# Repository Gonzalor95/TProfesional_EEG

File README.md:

# TProfesional_EEG

Trabajo Profesional para la carrera de Ingeniería Electrónica de FIUBA

Alumnos:
Rizzo Gonzalo
Davila Galesio Ignacio
Carosella Juan Manuel

Este repositorio contiene los archivos de software (codigo fuente y simulacion) generados para el trabajo final. Se divide en dos carpetas:

- CubeIDE_projects contiene los archivos relacionados a la programación y configuracion del microcontrolador junto con el software escrito para el mismo
- Proteus_projects contiene los archivos de simulacion

# Notas de reuniones

## 21/10/2021

Objetivo final: reproducción de muestras de 1 hora en total.
 * Agregar en la GUI la posibilidad de elegir el tiempo de reproducción
 * Considerar para el tema de la alimentación

Otras cuestiones:
* Analizar alternativas del BluePill. Capaz algo más potente, tiene más documentación, etc.
* Evaluar alternativa de mandar los datos de la PC al micro es utilizar en vez de USB, usar un protocolo inalámbrico. (ver si se puede realizar una adaptación para utilizar el celular para mandar los datos)
* Analizar Nice-to-have la utilización del celular para usar el dispositivo. Para este caso, es conveniente desarrollar la comunicación inalámbrica con el Microcontrolador.
* Analizar Linux driver: https://wiki.analog.com/resources/tools-software/linux-drivers/iio-dac/ad5360
 ** La familia de Nano puede ser que los drivers no sean solamente de Linux (investigar).
* Analizar el pin de LATCH en los DACs para sacar los datos de forma sincrónica. Si no hay Latch, investigar alternativa de como solucionarlo (enviar todos los canales de forma sincrónica).
* Analizar tambien que como el STM32 transmite a palabras de 16bits. Evaluar si podemos disminuir la resolución para lograr aprovechar esos 16 bits (en vez de enviar 2 palabras)
* Datasheet del DAC normalmente tiene la configuracion necesaria y podemos generar las funciones requeridas nosotros mismos para mejorar la performance.

## 23/9/2021

Microprocesador para experimentar: STM32F103c8t6 (BluePill)  

Simular alternativas:

-I2C: 
  * Definir si la baja velocidad del clock afecta significativamente la performance.
  * Simular un sistema lo más parecido posible a lo que nos proponemos. Es decir, debemos tener 32 salidas. En el caso de utilizar el LTC2631-HZ12 que solo tiene una salida y solo logra 9 direcciones, simular el caso de 32 canales repitiendo reiteradas veces la escritura en cada DAC.
  * Revisar si el Proteus no tiene un modelo con I2C con mayor cantidad de salidas.

-SPI:
  * En este caso, dado que el Blue Pill tiene solo 2 salidas de SPI disponibles, simular con un DAC con la mayor cantidad de salidas posibles.
  * La velocidad en este caso, no debería ser un factor limitante (REVISAR)

Definir cual conviene para proseguir. Pros y contras de cada una.

Comenzar a pensar las características importantes para el usuario (debe utilizar computadora, como se va a conectar al micro, como va a cargar las librerias, si se utiliza una memoria externa, etc)

Experimentar con la librería EDF, ver si en una simulación podemos obteenr un output utilizando dicha librería.

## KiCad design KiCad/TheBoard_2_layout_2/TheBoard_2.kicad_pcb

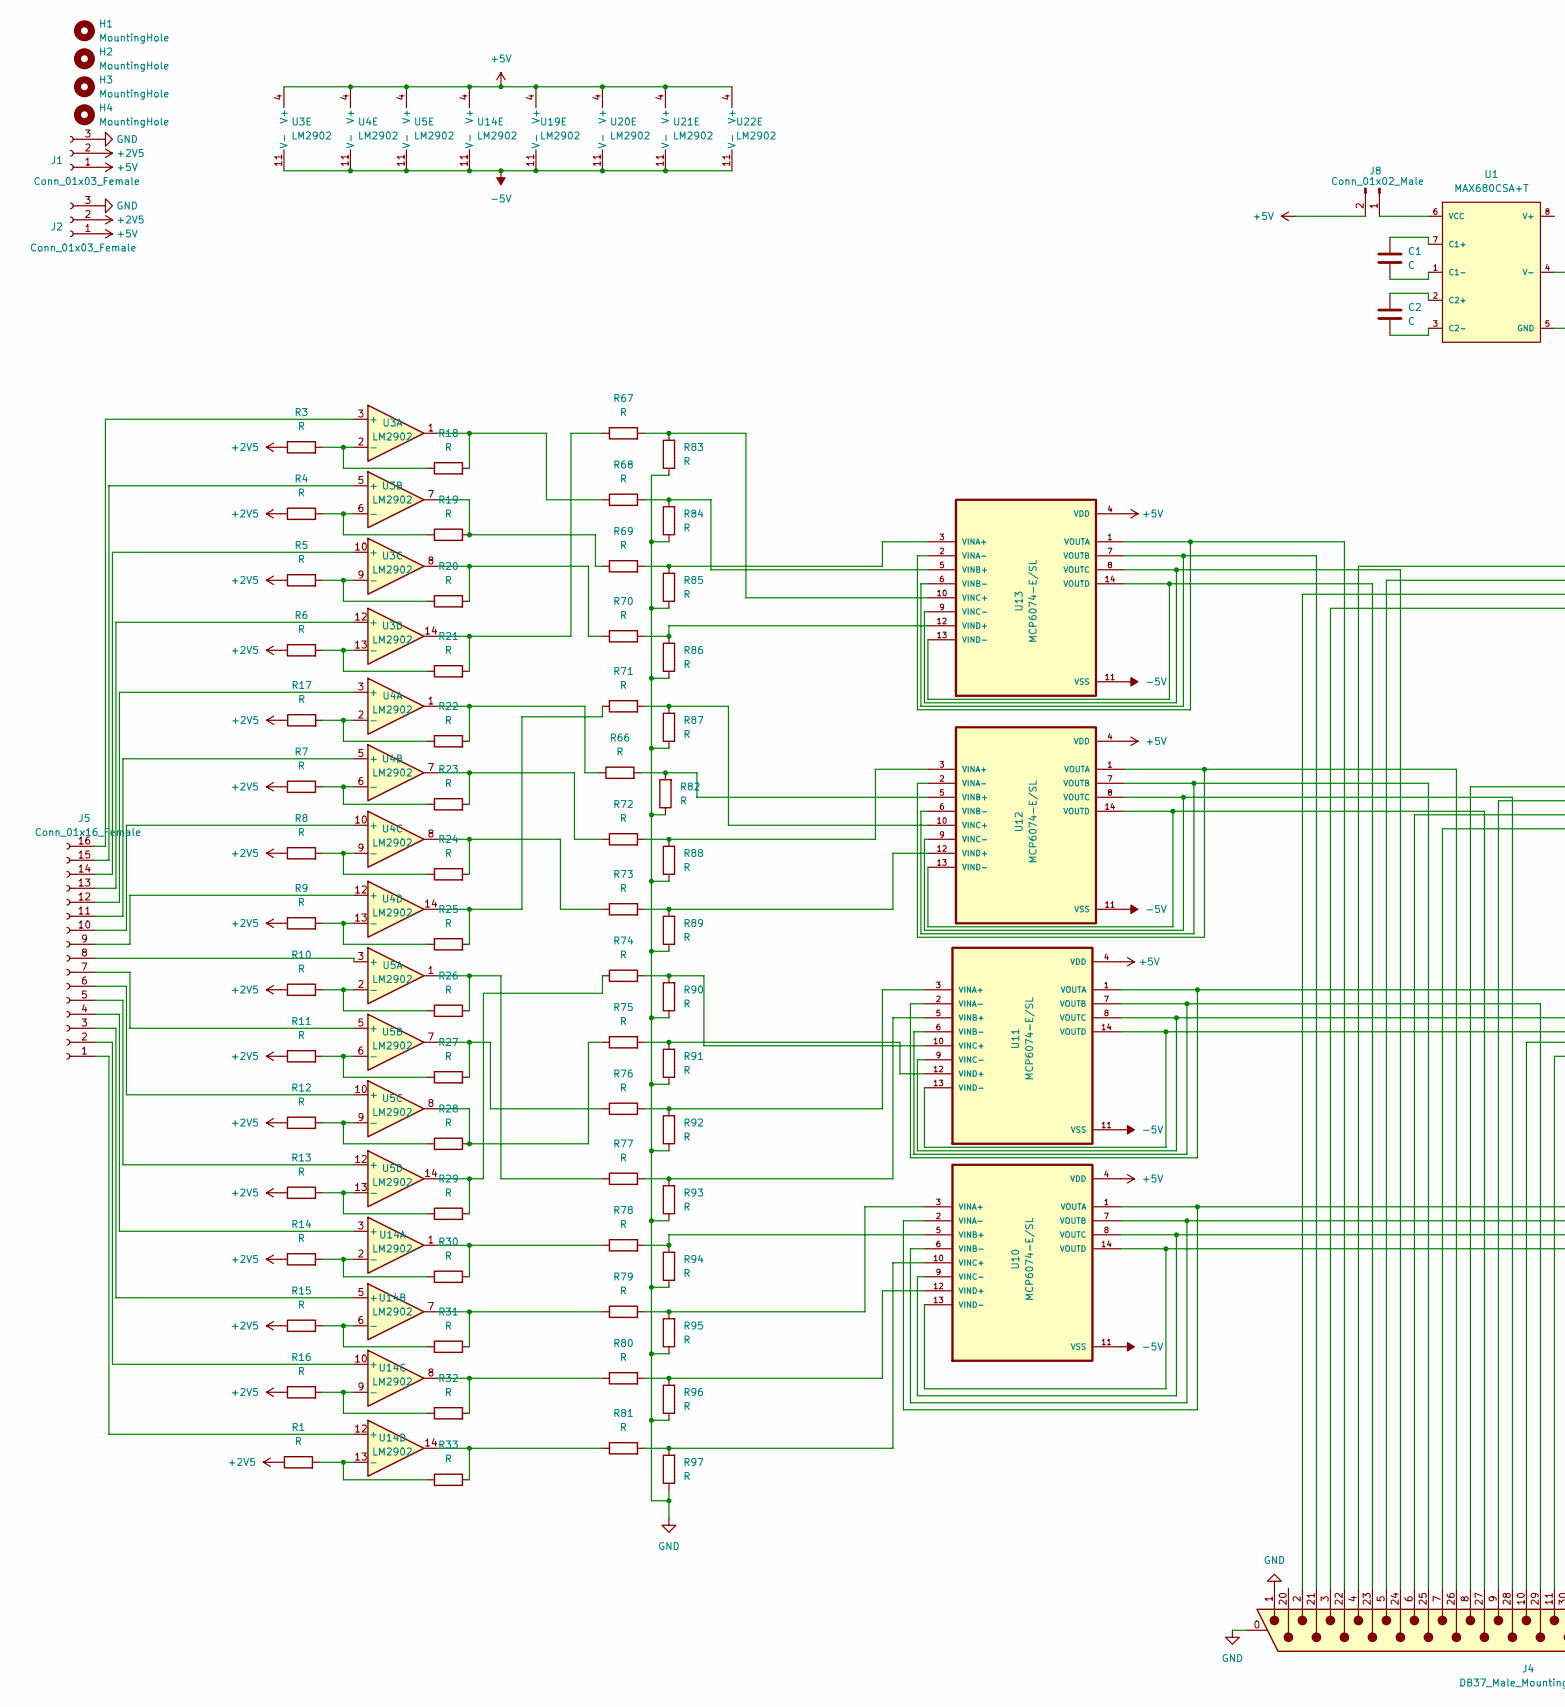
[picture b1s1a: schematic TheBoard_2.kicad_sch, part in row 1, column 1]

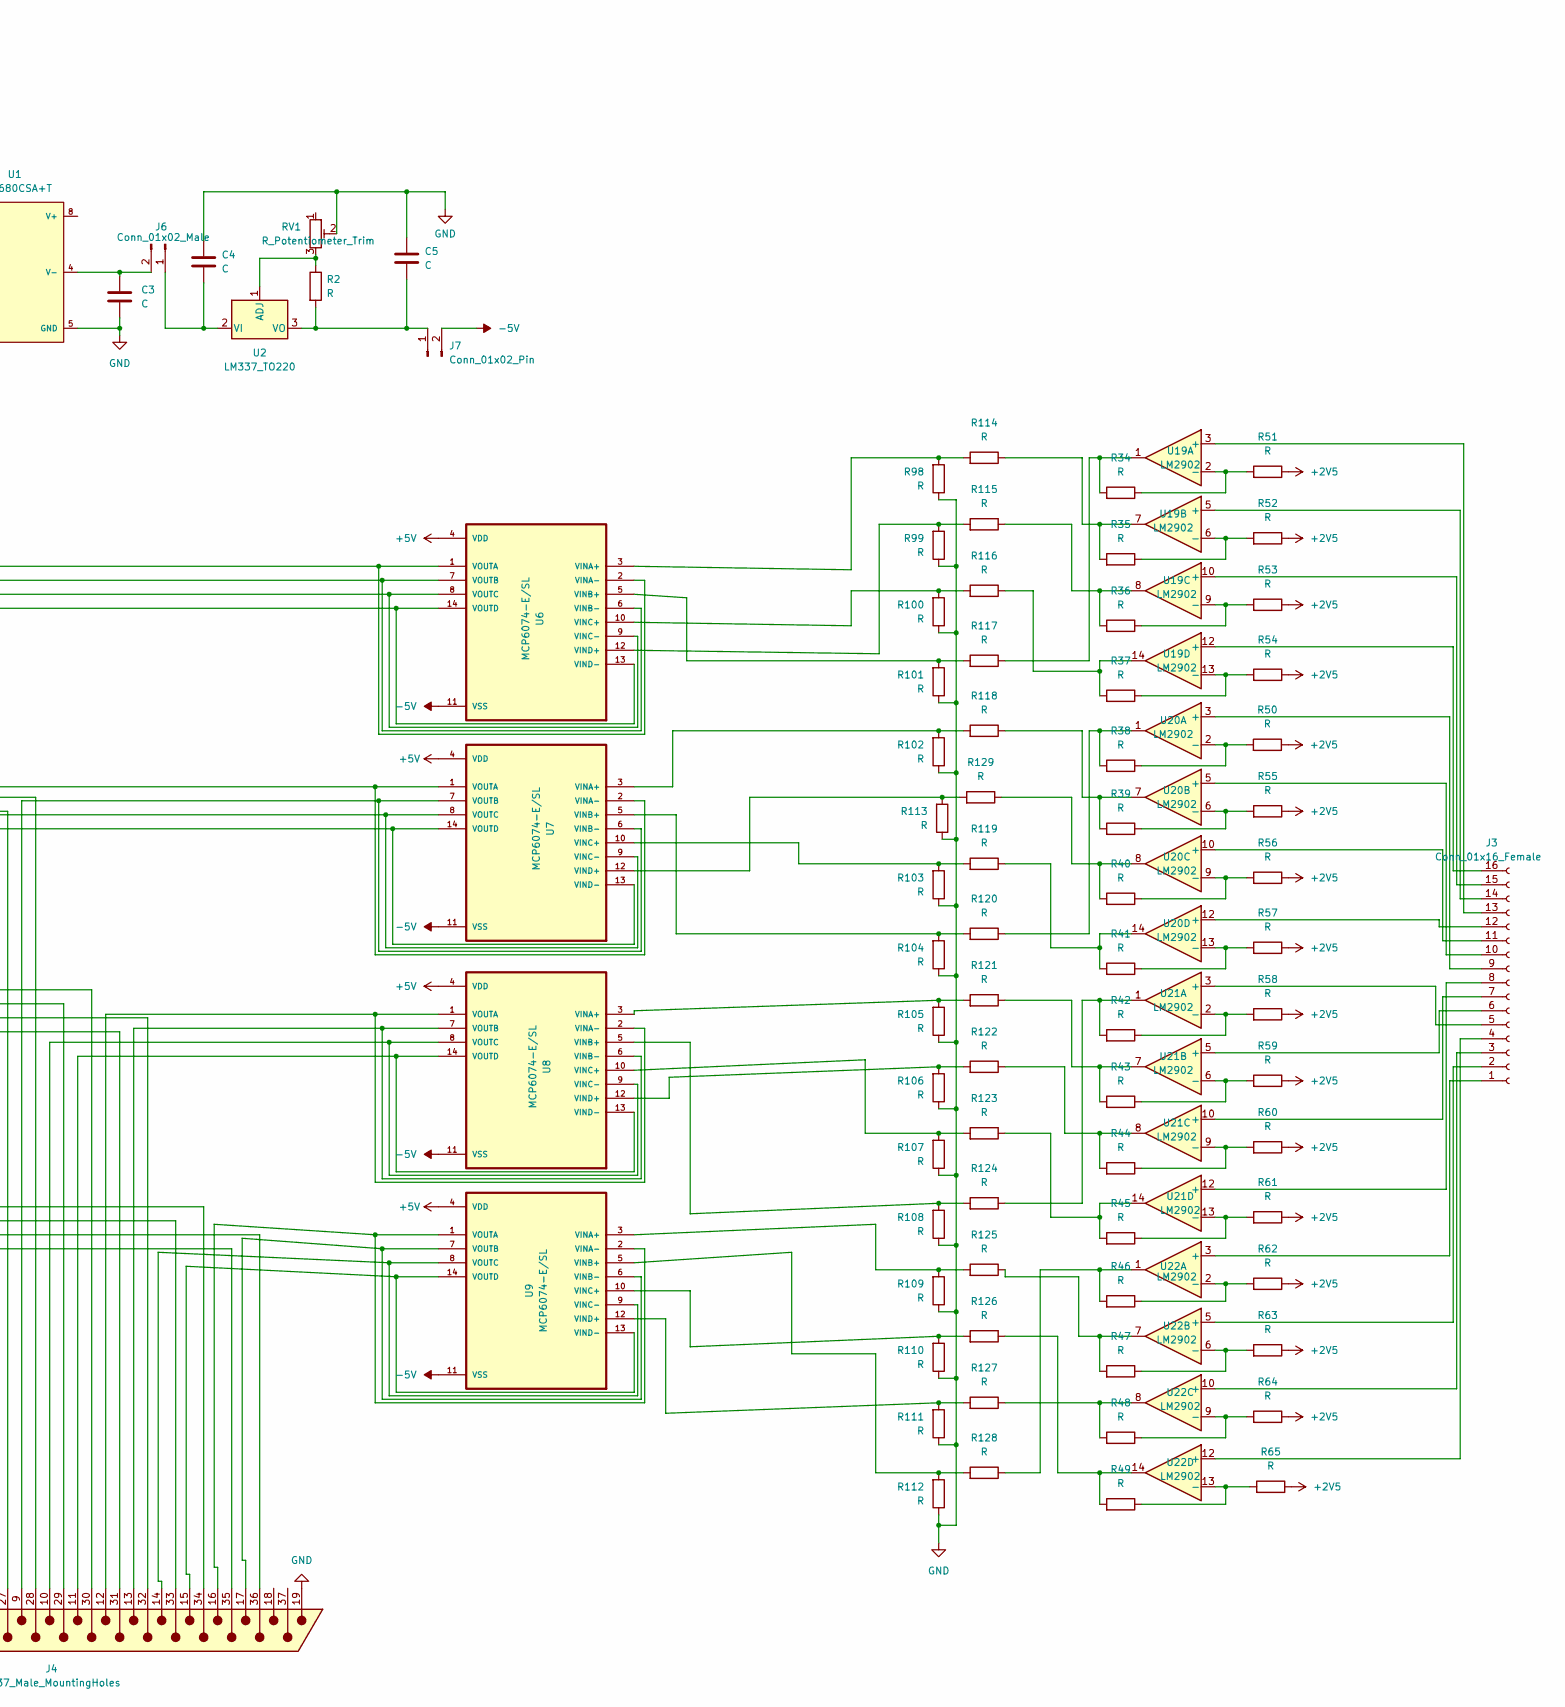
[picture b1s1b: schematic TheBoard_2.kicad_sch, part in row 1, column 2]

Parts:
C1, C2, C3, C4, C5: C; CP_Radial_D5.0mm_P2.00mm
H1, H2, H3, H4: MountingHole; MountingHole_3mm
J1, J2: Conn_01x03_Female; PinHeader_1x03_P2.54mm_Vertical
J3, J5: Conn_01x16_Female; PinSocket_1x16_P2.54mm_Vertical
J4: DB37_Male_MountingHoles; DSUB-37_Male_Horizontal_P2.77x2.84mm_EdgePinOffset7.70mm_Ho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
J6, J8: Conn_01x02_Male; PinHeader_1x02_P2.54mm_Vertical
J7: Conn_01x02_Pin; PinHeader_1x02_P2.54mm_Vertical
R1, R3, R4, R5, R6, R7, R8, R9, R10, R11, R12, R13, R14, R15, R16, R17, R18, R19, R20, R21, R22, R23, R24, R25, R26, R27, R28, R29, R30, R31, R32, R33, R34, R35, R36, R37, R38, R39, R40, R41, R42, R43, R44, R45, R46, R47, R48, R49, R50, R51, R52, R53, R54, R55, R56, R57, R58, R59, R60, R61, R62, R63, R64, R65, R66, R67, R68, R69, R70, R71, R72, R73, R74, R75, R76, R77, R78, R79, R80, R81, R82, R83, R84, R85, R86, R87, R88, R89, R90, R91, R92, R93, R94, R95, R96, R97, R98, R99, R100, R101, R102, R103, R104, R105, R106, R107, R108, R109, R110, R111, R112, R113, R114, R115, R116, R117, R118, R119, R120, R121, R122, R123, R124, R125, R126, R127, R128, R129: R; R_0805_2012Metric
R2: R; R_Axial_DIN0207_L6.3mm_D2.5mm_P7.62mm_Horizontal
RV1: R_Potentiometer_Trim; Potentiometer_Bourns_3296W_Vertical
U1: MAX680CSA+T; DIP-8_W7.62mm_LongPads; negative voltage availa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 true; output voltage 12V; mouser part number 700-MAX680CSAT; digikey description IC REG SWTCHD CAP INV 10MA 8SOIC
U2: LM337_TO220; TO-220-3_Vertical
U3, U4, U5, U14, U19, U20, U21, U22: LM2902; SOIC-14_3.9x8.7mm_P1.27mm
U6, U7, U8, U9, U10, U11, U12, U13: MCP6074-E/SL; SOIC-14_3.9x8.7mm_P1.27mm

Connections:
+2V5: J1.2, J2.2, R1.1, R3.1, R4.1, R5.1, R6.1, R7.1, R8.1, R9.1, R10.1, R11.1, R12.1, R13.1, R14.1, R15.1, R16.1, R17.1, R50.1, R51.1, R52.1, R53.1, R54.1, R55.1, R56.1, R57.1, R58.1, R59.1, R60.1, R61.1, R62.1, R63.1, R64.1, R65.1
+5V: J1.1, J2.1, J8.2, U3.4 (V+), U4.4 (V+), U5.4 (V+), U6.4 (VDD), U7.4 (VDD), U8.4 (VDD), U9.4 (VDD), U10.4 (VDD), U11.4 (VDD), U12.4 (VDD), U13.4 (VDD), U14.4 (V+), U19.4 (V+), U20.4 (V+), U21.4 (V+), U22.4 (V+)
-5V: J7.2, U3.11 (V-), U4.11 (V-), U5.11 (V-), U6.11 (VSS), U7.11 (VSS), U8.11 (VSS), U9.11 (VSS), U10.11 (VSS), U11.11 (VSS), U12.11 (VSS), U13.11 (VSS), U14.11 (V-), U19.11 (V-), U20.11 (V-), U21.11 (V-), U22.11 (V-)
GND: C3.2, C4.1, C5.1, J1.3, J2.3, J4.0 (PAD), J4.1, J4.19, R82.1, R83.1, R84.1, R85.1, R86.1, R87.1, R88.1, R89.1, R90.1, R91.1, R92.1, R93.1, R94.1, R95.1, R96.1, R97.1, R98.1, R99.1, R100.1, R101.1, R102.1, R103.1, R104.1, R105.1, R106.1, R107.1, R108.1, R109.1, R110.1, R111.1, R112.1, R113.1, RV1.1, RV1.2, U1.5 (GND)
unnamed: J3.1, U22.3 (+)
unnamed: J3.2, U22.5 (+)
unnamed: J3.3, U22.10 (+)
unnamed: J3.4, U22.12 (+)
unnamed: J3.5, U21.3 (+)
unnamed: J3.6, U21.5 (+)
unnamed: J3.7, U21.10 (+)
unnamed: J3.8, U21.12 (+)
unnamed: J3.9, U20.3 (+)
unnamed: J3.10, U20.5 (+)
unnamed: J3.11, U20.10 (+)
unnamed: J3.12, U20.12 (+)
unnamed: J3.13, U19.3 (+)
unnamed: J3.14, U19.5 (+)
unnamed: J3.15, U19.10 (+)
unnamed: J3.16, U19.12 (+)
unnamed: J5.1, U14.12 (+)
unnamed: J5.2, U14.10 (+)
unnamed: J5.3, U14.5 (+)
unnamed: J5.4, U14.3 (+)
unnamed: J5.5, U5.12 (+)
unnamed: J5.6, U5.10 (+)
unnamed: J5.7, U5.5 (+)
unnamed: J5.8, U5.3 (+)
unnamed: J5.9, U4.12 (+)
unnamed: J5.10, U4.10 (+)
unnamed: J5.11, U4.5 (+)
unnamed: J5.12, U4.3 (+)
unnamed: J5.13, U3.12 (+)
unnamed: J5.14, U3.10 (+)
unnamed: J5.15, U3.5 (+)
unnamed: J5.16, U3.3 (+)
unnamed: C4.2, J6.1, U2.2 (VI)
unnamed: C3.1, J6.2, U1.4 (V-)
unnamed: C5.2, J7.1, R2.2, U2.3 (VO)
unnamed: J8.1, U1.6 (VCC)
unnamed: R18.2, R68.1, U3.1
unnamed: R19.2, R69.1, U3.7
unnamed: R20.2, R70.1, U3.8
unnamed: R21.2, R67.1, U3.14
unnamed: R22.2, R66.1, U4.1
unnamed: R23.2, R72.1, U4.7
unnamed: R24.2, R73.1, U4.8
unnamed: R25.2, R71.1, U4.14
unnamed: R26.2, R77.1, U5.1
unnamed: R27.2, R76.1, U5.7
unnamed: R28.2, R75.1, U5.8
unnamed: R29.2, R74.1, U5.14
unnamed: R30.2, R78.1, U14.1
unnamed: R31.2, R79.1, U14.7
unnamed: R32.2, R80.1, U14.8
unnamed: R33.2, R81.1, U14.14
unnamed: R35.2, R114.1, U19.7
unnamed: R36.2, R115.1, U19.8
unnamed: R37.2, R116.1, U19.14
unnamed: R34.2, R117.1, U19.1
unnamed: R39.2, R118.1, U20.7
unnamed: R41.2, R119.1, U20.14
unnamed: R38.2, R120.1, U20.1
unnamed: R43.2, R121.1, U21.7
unnamed: R44.2, R122.1, U21.8
unnamed: R45.2, R123.1, U21.14
unnamed: R42.2, R124.1, U21.1
unnamed: R47.2, R125.1, U22.7
unnamed: R49.2, R126.1, U22.14
unnamed: R48.2, R127.1, U22.8
unnamed: R46.2, R128.1, U22.1
unnamed: R40.2, R129.1, U20.8
unnamed: C1.1, U1.7 (C1+)
unnamed: C1.2, U1.1 (C1-)
unnamed: C2.1, U1.2 (C2+)
unnamed: C2.2, U1.3 (C2-)
unnamed: R2.1, RV1.3, U2.1 (ADJ)
unnamed: R3.2, R18.1, U3.2 (-)
unnamed: R4.2, R19.1, U3.6 (-)
unnamed: R5.2, R20.1, U3.9 (-)
unnamed: R6.2, R21.1, U3.13 (-)
unnamed: R17.2, R22.1, U4.2 (-)
unnamed: R7.2, R23.1, U4.6 (-)
unnamed: R8.2, R24.1, U4.9 (-)
unnamed: R9.2, R25.1, U4.13 (-)
unnamed: R10.2, R26.1, U5.2 (-)
unnamed: R11.2, R27.1, U5.6 (-)
unnamed: R12.2, R28.1, U5.9 (-)
unnamed: R13.2, R29.1, U5.13 (-)
unnamed: R98.2, R114.2, U6.3 (VINA+)
unnamed: J4.4, U6.1 (VOUTA), U6.2 (VINA-)
unnamed: R101.2, R117.2, U6.5 (VINB+)
unnamed: J4.5, U6.6 (VINB-), U6.7 (VOUTB)
unnamed: R100.2, R116.2, U6.10 (VINC+)
unnamed: J4.2, U6.8 (VOUTC), U6.9 (VINC-)
unnamed: R99.2, R115.2, U6.12 (VIND+)
unnamed: J4.3, U6.13 (VIND-), U6.14 (VOUTD)
unnamed: R102.2, R118.2, U7.3 (VINA+)
unnamed: J4.8, U7.1 (VOUTA), U7.2 (VINA-)
unnamed: R104.2, R120.2, U7.5 (VINB+)
unnamed: J4.9, U7.6 (VINB-), U7.7 (VOUTB)
unnamed: R103.2, R119.2, U7.10 (VINC+)
unnamed: J4.6, U7.8 (VOUTC), U7.9 (VINC-)
unnamed: R113.2, R129.2, U7.12 (VIND+)
unnamed: J4.7, U7.13 (VIND-), U7.14 (VOUTD)
unnamed: R105.2, R121.2, U8.3 (VINA+)
unnamed: J4.12, U8.1 (VOUTA), U8.2 (VINA-)
unnamed: R108.2, R124.2, U8.5 (VINB+)
unnamed: J4.13, U8.6 (VINB-), U8.7 (VOUTB)
unnamed: R107.2, R123.2, U8.10 (VINC+)
unnamed: J4.10, U8.8 (VOUTC), U8.9 (VINC-)
unnamed: R106.2, R122.2, U8.12 (VIND+)
unnamed: J4.11, U8.13 (VIND-), U8.14 (VOUTD)
unnamed: R109.2, R125.2, U9.3 (VINA+)
unnamed: J4.16, U9.1 (VOUTA), U9.2 (VINA-)
unnamed: R112.2, R128.2, U9.5 (VINB+)
unnamed: J4.17, U9.6 (VINB-), U9.7 (VOUTB)
unnamed: R110.2, R126.2, U9.10 (VINC+)
unnamed: J4.14, U9.8 (VOUTC), U9.9 (VINC-)
unnamed: R111.2, R127.2, U9.12 (VIND+)
unnamed: J4.15, U9.13 (VIND-), U9.14 (VOUTD)
unnamed: R79.2, R95.2, U10.3 (VINA+)
unnamed: J4.34, U10.1 (VOUTA), U10.2 (VINA-)
unnamed: R78.2, R94.2, U10.5 (VINB+)
unnamed: J4.33, U10.6 (VINB-), U10.7 (VOUTB)
unnamed: R81.2, R97.2, U10.10 (VINC+)
unnamed: J4.36, U10.8 (VOUTC), U10.9 (VINC-)
unnamed: R80.2, R96.2, U10.12 (VIND+)
unnamed: J4.35, U10.13 (VIND-), U10.14 (VOUTD)
unnamed: R76.2, R92.2, U11.3 (VINA+)
unnamed: J4.30, U11.1 (VOUTA), U11.2 (VINA-)
unnamed: R77.2, R93.2, U11.5 (VINB+)
unnamed: J4.29, U11.6 (VINB-), U11.7 (VOUTB)
unnamed: R74.2, R90.2, U11.10 (VINC+)
unnamed: J4.32, U11.8 (VOUTC), U11.9 (VINC-)
unnamed: R75.2, R91.2, U11.12 (VIND+)
unnamed: J4.31, U11.13 (VIND-), U11.14 (VOUTD)
unnamed: R72.2, R88.2, U12.3 (VINA+)
unnamed: J4.26, U12.1 (VOUTA), U12.2 (VINA-)
unnamed: R66.2, R82.2, U12.5 (VINB+)
unnamed: J4.25, U12.6 (VINB-), U12.7 (VOUTB)
unnamed: R71.2, R87.2, U12.10 (VINC+)
unnamed: J4.28, U12.8 (VOUTC), U12.9 (VINC-)
unnamed: R73.2, R89.2, U12.12 (VIND+)
unnamed: J4.27, U12.13 (VIND-), U12.14 (VOUTD)
unnamed: R69.2, R85.2, U13.3 (VINA+)
unnamed: J4.22, U13.1 (VOUTA), U13.2 (VINA-)
unnamed: R68.2, R84.2, U13.5 (VINB+)
unnamed: J4.21, U13.6 (VINB-), U13.7 (VOUTB)
unnamed: R67.2, R83.2, U13.10 (VINC+)
unnamed: J4.24, U13.8 (VOUTC), U13.9 (VINC-)
unnamed: R70.2, R86.2, U13.12 (VIND+)
unnamed: J4.23, U13.13 (VIND-), U13.14 (VOUTD)
unnamed: R14.2, R30.1, U14.2 (-)
unnamed: R15.2, R31.1, U14.6 (-)
unnamed: R16.2, R32.1, U14.9 (-)
unnamed: R1.2, R33.1, U14.13 (-)
unnamed: R34.1, R51.2, U19.2 (-)
unnamed: R35.1, R52.2, U19.6 (-)
unnamed: R36.1, R53.2, U19.9 (-)
unnamed: R37.1, R54.2, U19.13 (-)
unnamed: R38.1, R50.2, U20.2 (-)
unnamed: R39.1, R55.2, U20.6 (-)
unnamed: R40.1, R56.2, U20.9 (-)
unnamed: R41.1, R57.2, U20.13 (-)
unnamed: R42.1, R58.2, U21.2 (-)
unnamed: R43.1, R59.2, U21.6 (-)
unnamed: R44.1, R60.2, U21.9 (-)
unnamed: R45.1, R61.2, U21.13 (-)
unnamed: R46.1, R62.2, U22.2 (-)
unnamed: R47.1, R63.2, U22.6 (-)
unnamed: R48.1, R64.2, U22.9 (-)
unnamed: R49.1, R65.2, U22.13 (-)

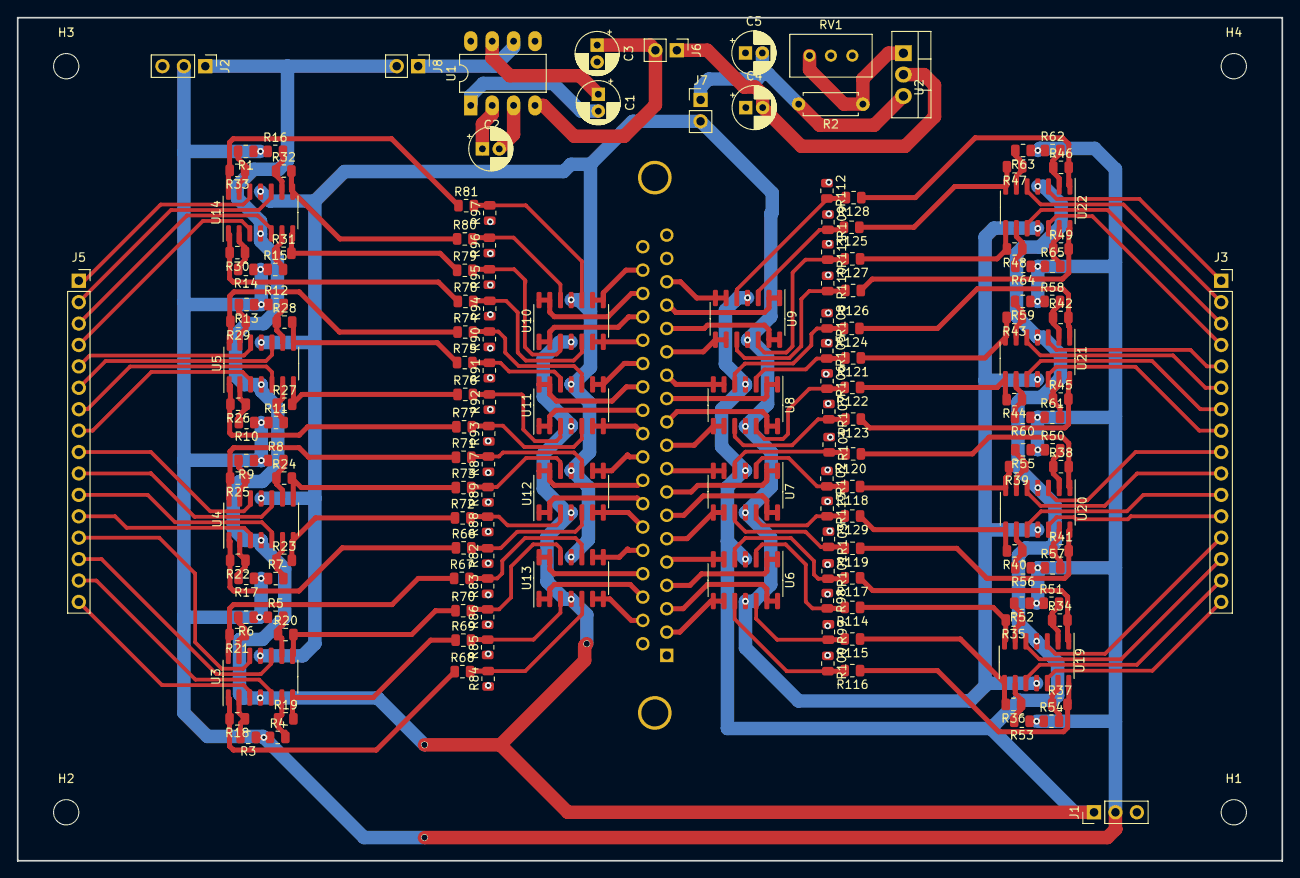
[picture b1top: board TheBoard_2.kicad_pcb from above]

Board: 2 copper layers, 150.0 x 100.0 mm, 165 parts (1 on the bottom side), 173 nets.

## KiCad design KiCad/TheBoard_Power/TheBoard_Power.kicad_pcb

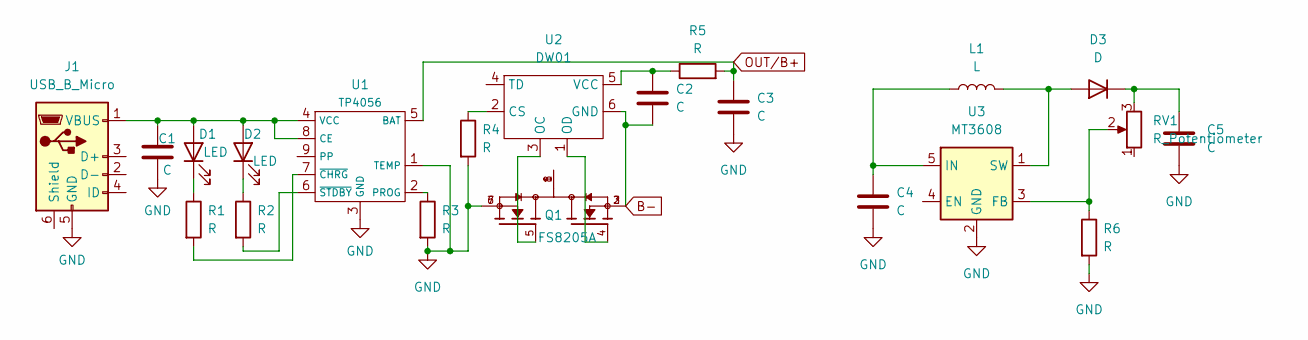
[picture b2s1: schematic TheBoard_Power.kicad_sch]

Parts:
C1, C2: C; C_0402_1005Metric_Pad0.74x0.62mm_HandSolder
C3: C; C_0603_1608Metric_Pad1.08x0.95mm_HandSolder
C4, C5: C; C_1206_3216Metric
D1, D2: LED; LED_0402_1005Metric_Pad0.77x0.64mm_HandSolder
D3: D; D_SMA
J1: USB_B_Micro; USB_Micro-B_Molex_47346-0001
L1: L; L_10.4x10.4_H4.8
Q1: FS8205A; TSSOP-8_4.4x3mm_P0.65mm; PARTREV 1.7
R1, R2, R3, R4, R5: R; R_0402_1005Metric_Pad0.72x0.64mm_HandSolder
R6: R; R_0805_2012Metric
RV1: R_Potentiometer; Potentiometer_Bourns_3296P_Horizontal
U1: TP4056; SOIC-8-1EP_3.9x4.9mm_P1.27mm_EP2.29x3mm
U2: DW01; SOT-23-6_Handsoldering
U3: MT3608; SOT-23-6

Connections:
B-: C2.2, Q1.2, Q1.3, U2.6 (GND)
GND: C1.2, C3.2, C4.2, C5.2, J1.5 (GND), Q1.6, Q1.7, R3.2, R4.2, R6.2, U1.1 (TEMP), U1.3 (GND), U3.2 (GND)
unnamed: C1.1, D1.2 (A), D2.2 (A), J1.1 (VBUS), U1.4 (VCC), U1.8 (CE)
unnamed: C2.1, R5.1, U2.5 (VCC)
unnamed: C4.1, L1.1, U3.5 (IN)
unnamed: C5.1, D3.1 (K), RV1.3
unnamed: D1.1 (K), R1.1
unnamed: D2.1 (K), R2.1
unnamed: D3.2 (A), L1.2, U3.1 (SW)
unnamed: Q1.1, Q1.8
unnamed: Q1.4, U2.1 (OD)
unnamed: Q1.5, U2.3 (OC)
unnamed: R1.2, U1.7 (~CHRG)
unnamed: R2.2, U1.6 (~STDBY)
unnamed: R3.1, U1.2 (PROG)
unnamed: R4.1, U2.2 (CS)
unnamed: R6.1, RV1.2, U3.3 (FB)
OUT/B+: C3.1, R5.2, U1.5 (BAT)

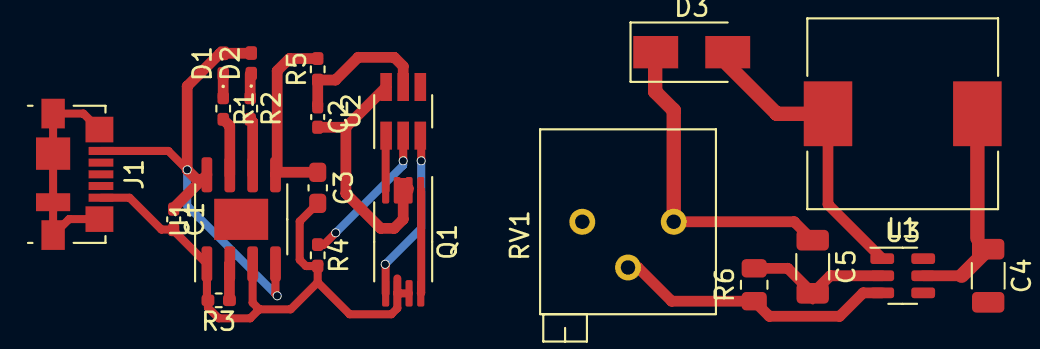
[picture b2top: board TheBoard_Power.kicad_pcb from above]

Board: 2 copper layers, 21 parts (0 on the bottom side), 18 nets.

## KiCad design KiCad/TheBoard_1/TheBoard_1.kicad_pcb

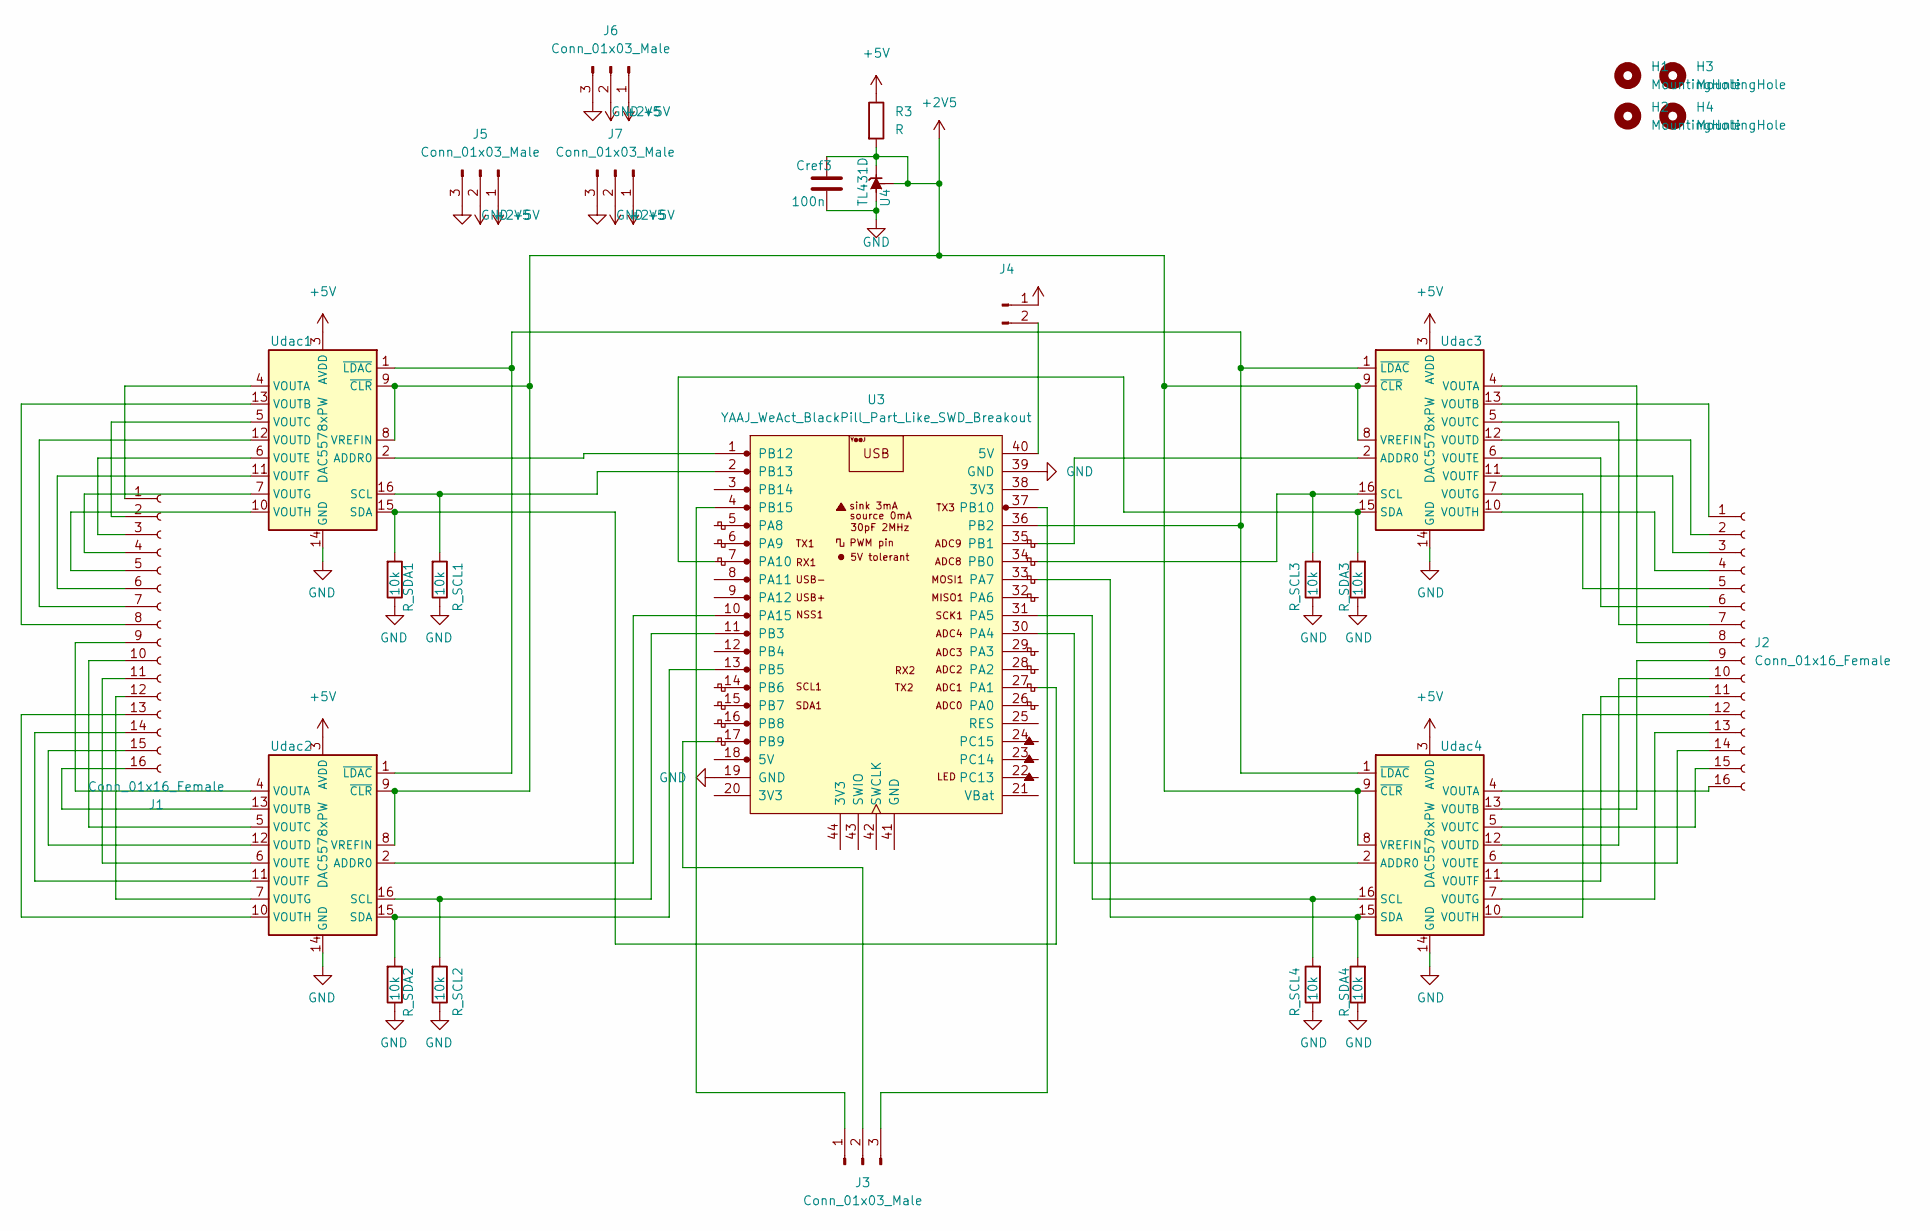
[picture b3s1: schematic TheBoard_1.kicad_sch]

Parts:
Cref3: 100n; C_Disc_D5.0mm_W2.5mm_P2.50mm
H1, H2, H3, H4: MountingHole; MountingHole_3mm
J1, J2: Conn_01x16_Female; PinHeader_1x16_P2.54mm_Vertical
J3, J5, J6, J7: Conn_01x03_Male; PinHeader_1x03_P2.54mm_Vertical
J4: (no value)
R3: R; R_Axial_DIN0207_L6.3mm_D2.5mm_P10.16mm_Horizontal
R_SCL1, R_SCL2, R_SCL3, R_SCL4: 10k; R_Axial_DIN0207_L6.3mm_D2.5mm_P10.16mm_Horizontal
R_SDA1, R_SDA2, R_SDA3, R_SDA4: 10k; R_Axial_DIN0207_L6.3mm_D2.5mm_P10.16mm_Horizontal
U3: YAAJ_WeAct_BlackPill_Part_Like_SWD_Breakout; YAAJ_WeAct_BlackPill_SWD_2
U4: TL431D; SOIC-8_3.9x4.9mm_P1.27mm
Udac1, Udac2, Udac3, Udac4: DAC5578xPW; TSSOP-16_4.4x5mm_P0.65mm

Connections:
+2V5: Cref3.1, J5.2, J6.2, J7.2, R3.2, U4.1 (K), U4.8 (REF), Udac1.8 (VREFIN), Udac1.9 (~CLR), Udac2.8 (VREFIN), Udac2.9 (~CLR), Udac3.8 (VREFIN), Udac3.9 (~CLR), Udac4.8 (VREFIN), Udac4.9 (~CLR)
GND: Cref3.2, J5.3, J6.3, J7.3, R_SCL1.1, R_SCL2.1, R_SCL3.1, R_SCL4.1, R_SDA1.1, R_SDA2.1, R_SDA3.1, R_SDA4.1, U3.19 (GND), U3.39 (GND), U4.2 (A), U4.3 (A), U4.6 (A), U4.7 (A), Udac1.14 (GND), Udac2.14 (GND), Udac3.14 (GND), Udac4.14 (GND)
unnamed: J1.1, Udac1.4 (VOUTA)
unnamed: J1.2, Udac1.5 (VOUTC)
unnamed: J1.3, Udac1.6 (VOUTE)
unnamed: J1.4, Udac1.7 (VOUTG)
unnamed: J1.5, Udac1.10 (VOUTH)
unnamed: J1.6, Udac1.11 (VOUTF)
unnamed: J1.7, Udac1.12 (VOUTD)
unnamed: J1.8, Udac1.13 (VOUTB)
unnamed: J1.9, Udac2.4 (VOUTA)
unnamed: J1.10, Udac2.5 (VOUTC)
unnamed: J1.11, Udac2.6 (VOUTE)
unnamed: J1.12, Udac2.7 (VOUTG)
unnamed: J1.13, Udac2.10 (VOUTH)
unnamed: J1.14, Udac2.11 (VOUTF)
unnamed: J1.15, Udac2.12 (VOUTD)
unnamed: J1.16, Udac2.13 (VOUTB)
unnamed: J2.1, Udac3.13 (VOUTB)
unnamed: J2.2, Udac3.12 (VOUTD)
unnamed: J2.3, Udac3.11 (VOUTF)
unnamed: J2.4, Udac3.10 (VOUTH)
unnamed: J2.5, Udac3.7 (VOUTG)
unnamed: J2.6, Udac3.6 (VOUTE)
unnamed: J2.7, Udac3.5 (VOUTC)
unnamed: J2.8, Udac3.4 (VOUTA)
unnamed: J2.9, Udac4.13 (VOUTB)
unnamed: J2.10, Udac4.12 (VOUTD)
unnamed: J2.11, Udac4.11 (VOUTF)
unnamed: J2.12, Udac4.10 (VOUTH)
unnamed: J2.13, Udac4.7 (VOUTG)
unnamed: J2.14, Udac4.6 (VOUTE)
unnamed: J2.15, Udac4.5 (VOUTC)
unnamed: J2.16, Udac4.4 (VOUTA)
unnamed: J3.1, U3.4 (PB15)
unnamed: J3.2, U3.17 (PB9)
unnamed: J3.3, U3.37 (PB10)
unnamed: J4.2, U3.40 (5V)
unnamed: R_SCL1.2, U3.2 (PB13), Udac1.16 (SCL)
unnamed: R_SCL2.2, U3.11 (PB3), Udac2.16 (SCL)
unnamed: R_SCL3.2, U3.34 (PB0), Udac3.16 (SCL)
unnamed: R_SCL4.2, U3.31 (PA5), Udac4.16 (SCL)
unnamed: R_SDA1.2, U3.27 (PA1), Udac1.15 (SDA)
unnamed: R_SDA2.2, U3.13 (PB5), Udac2.15 (SDA)
unnamed: R_SDA3.2, U3.7 (PA10), Udac3.15 (SDA)
unnamed: R_SDA4.2, U3.33 (PA7), Udac4.15 (SDA)
unnamed: U3.1 (PB12), Udac1.2 (ADDR0)
unnamed: U3.10 (PA15), Udac2.2 (ADDR0)
unnamed: U3.30 (PA4), Udac4.2 (ADDR0)
unnamed: U3.35 (PB1), Udac3.2 (ADDR0)
unnamed: U3.36 (PB2), Udac1.1 (~LDAC), Udac2.1 (~LDAC), Udac3.1 (~LDAC), Udac4.1 (~LDAC)

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
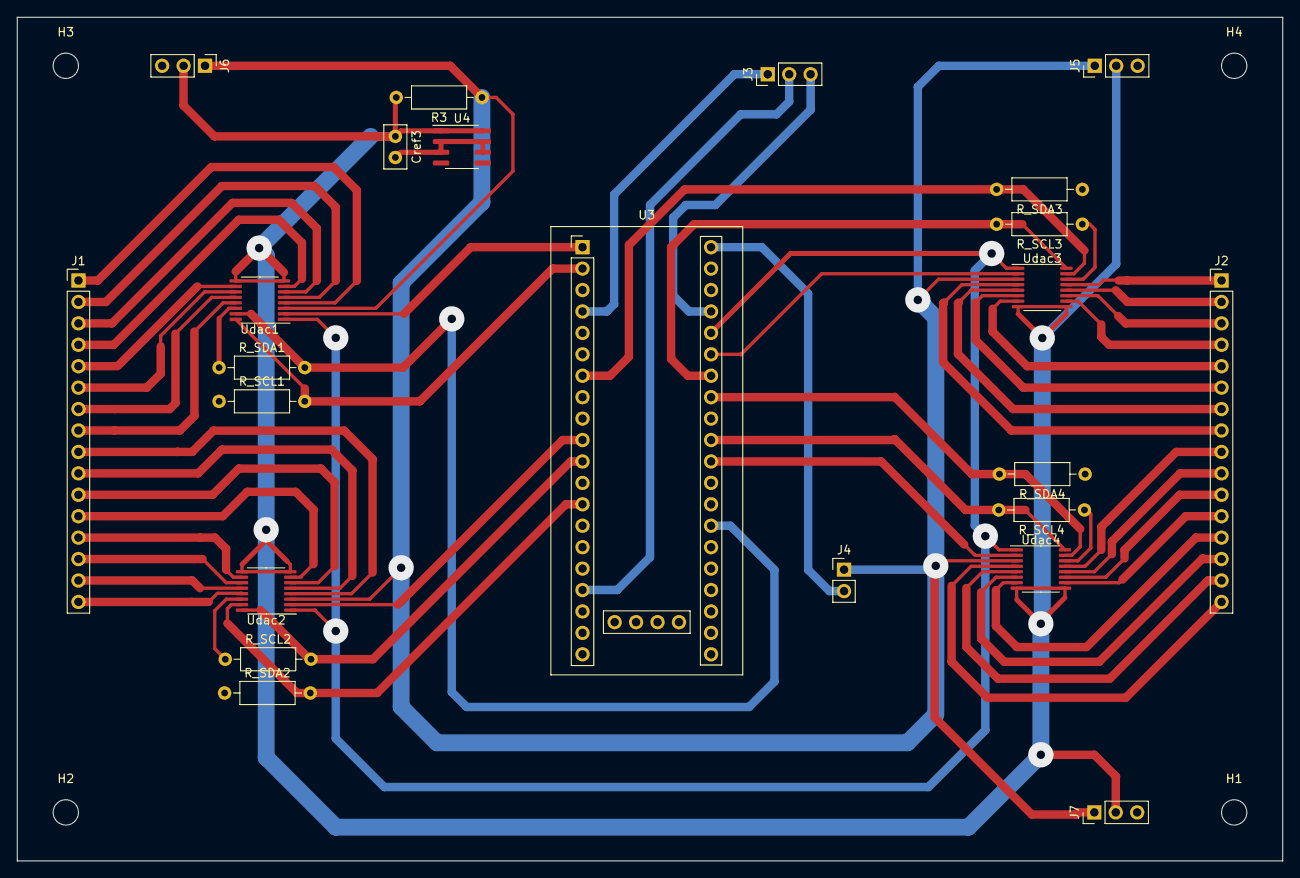
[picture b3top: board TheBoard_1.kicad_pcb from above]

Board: 2 copper layers, 150.0 x 100.0 mm, 27 parts (0 on the bottom side), 52 nets.

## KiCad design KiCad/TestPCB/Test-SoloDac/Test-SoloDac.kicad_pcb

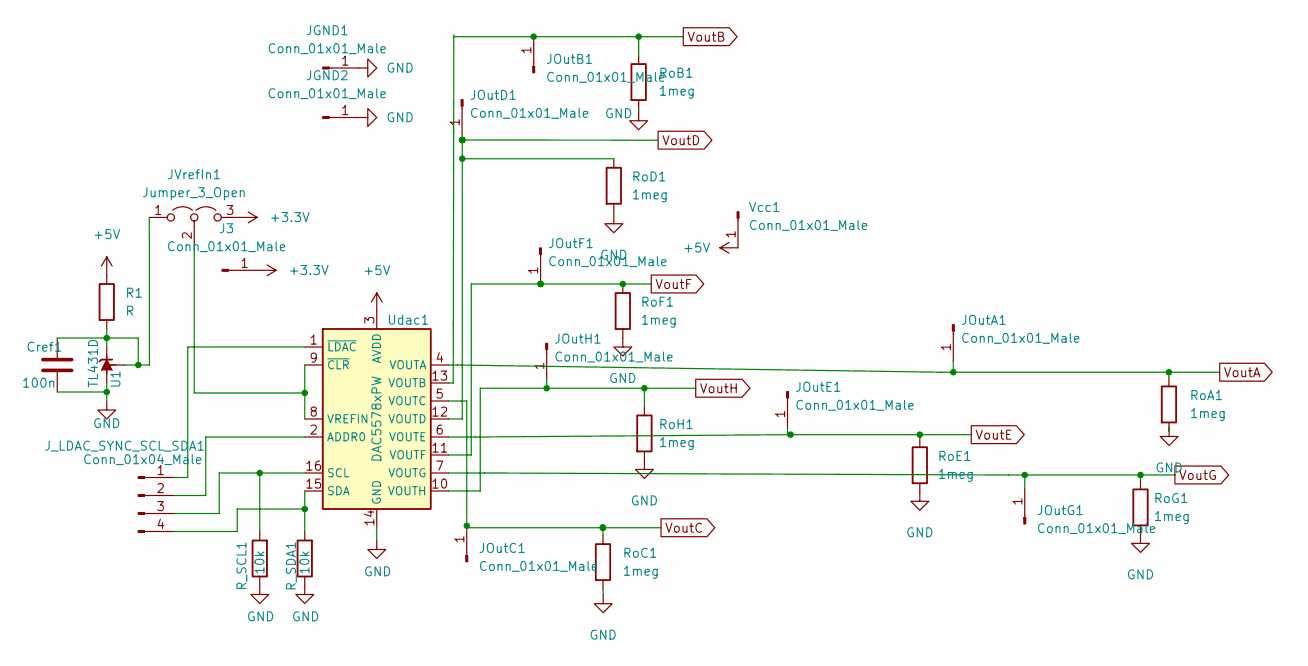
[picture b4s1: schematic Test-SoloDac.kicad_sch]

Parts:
Cref1: 100n; C_Disc_D5.0mm_W2.5mm_P2.50mm
J3: Conn_01x01_Male; PinHeader_1x01_P2.54mm_Vertical
JGND1, JGND2: Conn_01x01_Male; PinHeader_1x01_P2.54mm_Vertical
JOutA1: Conn_01x01_Male; PinHeader_1x01_P2.54mm_Vertical
JOutB1: Conn_01x01_Male; PinHeader_1x01_P2.54mm_Vertical
JOutC1: Conn_01x01_Male; PinHeader_1x01_P2.54mm_Vertical
JOutD1: Conn_01x01_Male; PinHeader_1x01_P2.54mm_Vertical
JOutE1: Conn_01x01_Male; PinHeader_1x01_P2.54mm_Vertical
JOutF1: Conn_01x01_Male; PinHeader_1x01_P2.54mm_Vertical
JOutG1: Conn_01x01_Male; PinHeader_1x01_P2.54mm_Vertical
JOutH1: Conn_01x01_Male; PinHeader_1x01_P2.54mm_Vertical
JVrefIn1: Jumper_3_Open; PinHeader_1x03_P2.54mm_Vertical
J_LDAC_SYNC_SCL_SDA1: Conn_01x04_Male; PinHeader_1x04_P2.54mm_Vertical
R1: R; R_Axial_DIN0207_L6.3mm_D2.5mm_P10.16mm_Horizontal
R_SCL1: 10k; R_Axial_DIN0207_L6.3mm_D2.5mm_P10.16mm_Horizontal
R_SDA1: 10k; R_Axial_DIN0207_L6.3mm_D2.5mm_P10.16mm_Horizontal
RoA1: 1meg; R_Axial_DIN0207_L6.3mm_D2.5mm_P10.16mm_Horizontal
RoB1: 1meg; R_Axial_DIN0207_L6.3mm_D2.5mm_P10.16mm_Horizontal
RoC1: 1meg; R_Axial_DIN0207_L6.3mm_D2.5mm_P10.16mm_Horizontal
RoD1: 1meg; R_Axial_DIN0207_L6.3mm_D2.5mm_P10.16mm_Horizontal
RoE1: 1meg; R_Axial_DIN0207_L6.3mm_D2.5mm_P10.16mm_Horizontal
RoF1: 1meg; R_Axial_DIN0207_L6.3mm_D2.5mm_P10.16mm_Horizontal
RoG1: 1meg; R_Axial_DIN0207_L6.3mm_D2.5mm_P10.16mm_Horizontal
RoH1: 1meg; R_Axial_DIN0207_L6.3mm_D2.5mm_P10.16mm_Horizontal
U1: TL431D; SOIC-8_3.9x4.9mm_P1.27mm
Udac1: DAC5578xPW; TSSOP-16_4.4x5mm_P0.65mm
Vcc1: Conn_01x01_Male; PinHeader_1x01_P2.54mm_Vertical

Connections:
+3V3: J3.1, JVrefIn1.3 (B)
+5V: R1.1, Udac1.3 (AVDD), Vcc1.1
GND: Cref1.2, JGND1.1, JGND2.1, R_SCL1.1, R_SDA1.1, RoA1.2, RoB1.2, RoC1.2, RoD1.2, RoE1.2, RoF1.2, RoG1.2, RoH1.2, U1.2 (A), U1.3 (A), U1.6 (A), U1.7 (A), Udac1.14 (GND)
unnamed: Cref1.1, JVrefIn1.1 (A), R1.2, U1.1 (K), U1.8 (REF)
unnamed: JVrefIn1.2 (C), Udac1.8 (VREFIN), Udac1.9 (~CLR)
unnamed: J_LDAC_SYNC_SCL_SDA1.1, Udac1.1 (~LDAC)
unnamed: J_LDAC_SYNC_SCL_SDA1.2, Udac1.2 (ADDR0)
unnamed: J_LDAC_SYNC_SCL_SDA1.3, R_SCL1.2, Udac1.16 (SCL)
unnamed: J_LDAC_SYNC_SCL_SDA1.4, R_SDA1.2, Udac1.15 (SDA)
VoutA: JOutA1.1, RoA1.1, Udac1.4 (VOUTA)
VoutB: JOutB1.1, RoB1.1, Udac1.13 (VOUTB)
VoutC: JOutC1.1, RoC1.1, Udac1.5 (VOUTC)
VoutD: JOutD1.1, RoD1.1, Udac1.12 (VOUTD)
VoutE: JOutE1.1, RoE1.1, Udac1.6 (VOUTE)
VoutF: JOutF1.1, RoF1.1, Udac1.11 (VOUTF)
VoutG: JOutG1.1, RoG1.1, Udac1.7 (VOUTG)
VoutH: JOutH1.1, RoH1.1, Udac1.10 (VOUTH)
